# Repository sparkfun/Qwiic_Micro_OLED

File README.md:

SparkFun SparkFun Micro OLED Breakout (Qwiic)
========================================

[*SparkFun Micro OLED Breakout (Qwiic) (LCD-22495)*](https://www.sparkfun.com/products/22495)

The SparkFun Qwiic Micro OLED Breakout is a Qwiic-enabled version of our popular Micro OLED display! The small monochrome, blue-on-black OLED screen presents incredibly clear images for your viewing pleasure. 

Repository Contents
-------------------

* **/Hardware** - Eagle design files (.brd, .sch)
* **/Libraries** - Libraries for use with the SparkFun Micro OLED Breakout (Qwiic)
* **/Production** - Production panel files (.brd)
* **/Software** - Related software for the SparkFun Micro OLED Breakout (Qwiic).

Documentation
--------------
* **[Micro OLED Breakout Library](https://github.com/sparkfun/SparkFun_Micro_OLED_Arduino_Library)** - Latest Arduino library for the Micro OLED Breakout.
* **[Qwiic Micro OLED Breakout Library](https://github.com/sparkfun/SparkFun_Qwiic_OLED_Arduino_Library)** - Alternative Arduino library for the Qwiic Micro OLED Breakout. This library is higher performance and handles memory better than the Micro OLED Arduino Library. This library also works with 2x other Qwiic OLEDs!!!
* **[SparkFun Fritzing Part](https://github.com/sparkfun/Fritzing_Parts/blob/main/products/22495_sfe_qwiic_micro_oled_breakout_top_view.fzpz)** - V11, top view
* **[SparkFun Fritzing Part](https://github.com/sparkfun/Fritzing_Parts/blob/main/products/14532_sfe_Qwiic_OLED_Breakout.fzpz)** - V10, bottom view
* **[Hookup Guide](https://learn.sparkfun.com/tutorials/qwiic-micro-oled-hookup-guide)** - Basic hookup guide for the SparkFun Micro OLED Breakout (Qwiic).

Product Versions
----------------
* [LCD-22495](https://www.sparkfun.com/products/22495) - SparkFun Qwiic Micro OLED Breakout, v11
* [LCD-14532](https://www.sparkfun.com/products/14532) - SparkFun Qwiic Micro OLED Breakout, v10
* [SPX-14269 (RETIRED)](https://www.sparkfun.com/products/14269) - SparkX Qwiic Micro OLED Breakout

License Information
-------------------

This product is _**open source**_! 

Please review the LICENSE.md file for license information. 

If you have any questions or concerns on licensing, please contact techsupport@sparkfun.com.

Distributed as-is; no warranty is given.

- Your friends at SparkFun.

_<COLLABORATION CREDIT>_

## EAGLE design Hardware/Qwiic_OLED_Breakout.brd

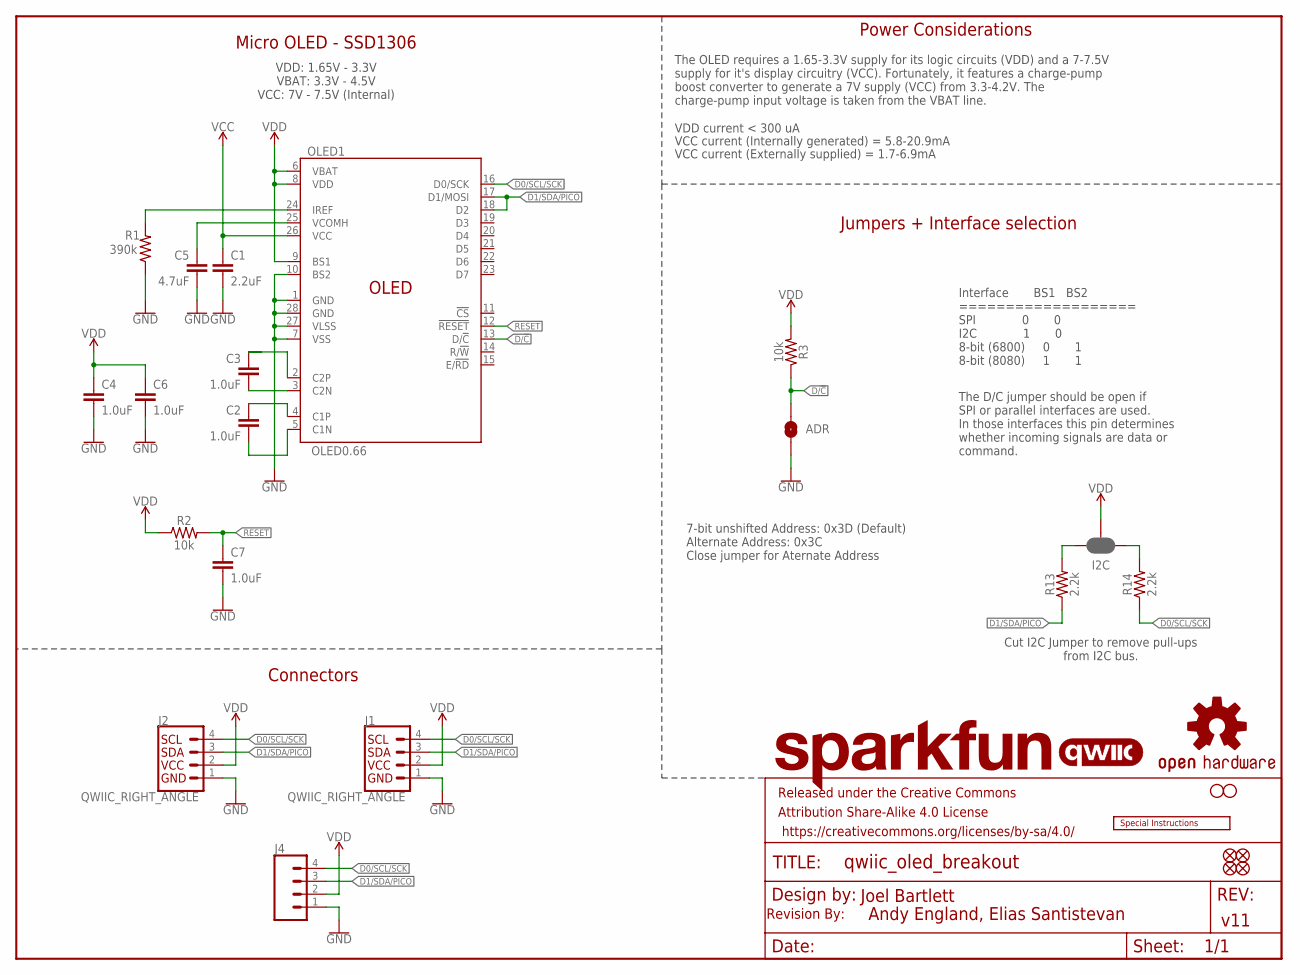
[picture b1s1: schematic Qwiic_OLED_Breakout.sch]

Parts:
ADR: JUMPER-SMT_2_NO_SILK; SMT-JUMPER_2_NO_SILK
C1: 2.2uF; 0805
C2, C3: 1.0uF; 0805
C4, C6, C7: 1.0uF; 0603
C5: 4.7uF; 1206
FID1, FID2, FID3, FID4: FIDUCIAL1X2; FIDUCIAL-1X2
FRAME1: FRAME-LETTER; CREATIVE_COMMONS
H1, H2: STAND-OFF
I2C: JUMPER-SMT_3_2-NC_PASTE_SILK; SMT-JUMPER_3_2-NC_PASTE_SILK
J1, J2: QWIIC_RIGHT_ANGLE; JST04_1MM_RA
J4: CONN_041X04_NO_SILK_NO_POP; 1X04_NO_SILK
LOGO2: SFE_LOGO_NAME.1_INCH; SFE_LOGO_NAME_.1
LOGO3: OSHW-LOGOS; OSHW-LOGO-S
LOGO5: QWIIC_LOGO_4MM; QWIIC_4MM
LOGO6: SPECIAL_INSTRUCTIONS-ORDERING; ORDERING_INSTRUCTIONS
OLED1: OLED0.66; OLED-0.66-64X48
R1: 390k; 0603
R2, R3: 10k; 0603
R13, R14: 2.2k; 0603

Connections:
C1P: C2.1, OLED1.4 (C1P)
C2N: C3.2, OLED1.3 (C2N)
D0/SCL/SCK: J1.4, J2.4, J4.4, OLED1.16 (D0/SCK), R14.1
D1/SDA/PICO: J1.3, J2.3, J4.3, OLED1.17 (D1/MOSI), OLED1.18 (D2), R13.1
D/!C!: ADR.2, OLED1.13 (D/!C!), R3.1
GND: ADR.1, C1.2, C4.2, C5.2, C6.2, C7.2, J1.1, J2.1, J4.1, OLED1.1 (GND), OLED1.7 (VSS), OLED1.10 (BS2), OLED1.27 (VLSS), OLED1.28 (GND), R1.1
IREF: OLED1.24 (IREF), R1.2
unnamed: C3.1, OLED1.2 (C2P)
unnamed: C2.2, OLED1.5 (C1N)
unnamed: I2C.3, R13.2
unnamed: I2C.1, R14.2
RESET: C7.1, OLED1.12 (!RESET!), R2.2
VCC: C1.1, OLED1.26 (VCC)
VCOMH: C5.1, OLED1.25 (VCOMH)
VDD: C4.1, C6.1, I2C.2, J1.2, J2.2, J4.2, OLED1.6 (VBAT), OLED1.8 (VDD), OLED1.9 (BS1), R2.1, R3.2

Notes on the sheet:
v11
VDD: 1.65V - 3.3V VBAT: 3.3V - 4.5V VCC: 7V - 7.5V (Internal)
VDD current < 300 uA
VCC current (Internally generated) = 5.8-20.9mA
VCC current (Externally supplied) = 1.7-6.9mA
Interface BS1 BS2 =================== SPI 0 0 I2C 1 0 8-bit (6800) 0 1 8-bit (8080) 1 1
Jumpers + Interface selection
7-bit unshifted Address: 0x3D (Default) Alternate Address: 0x3C Close jumper for Aternate Address
Power Considerations
The OLED requires a 1.65-3.3V supply for its logic circuits (VDD) and a 7-7.5V supply for it's display circuitry (VCC). Fortunately, it features a charge-pump boost converter to generate a 7V supply (VCC) from 3.3-4.2V. The charge-pump input voltage is taken from the VBAT line.
The D/C jumper should be open if SPI or parallel interfaces are used. In those interfaces this pin determines whether incoming signals are data or command.
Cut I2C Jumper to remove pull-ups from I2C bus.
Joel Bartlett
Andy England, Elias Santistevan
Connectors
Micro OLED - SSD1306
Revision By:

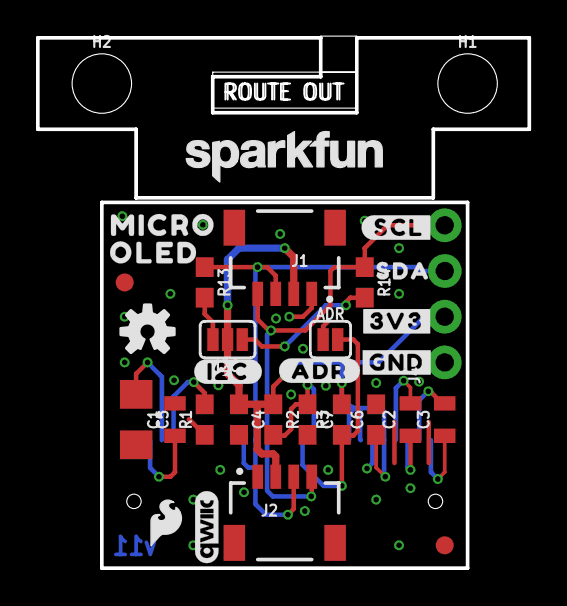
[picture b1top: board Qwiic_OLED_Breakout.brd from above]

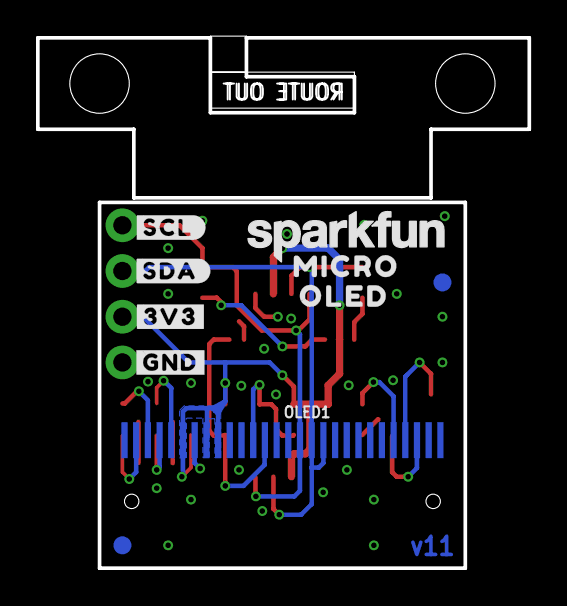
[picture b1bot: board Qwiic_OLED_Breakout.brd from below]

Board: 2 copper layers, 27.3 x 29.6 mm, 45 parts (10 on the bottom side), 15 nets.

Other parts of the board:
LOGO4: SFE_LOGO_NAME.1_INCH; SFE_LOGO_NAME_.1
U$1, U$13: MICRO593420
U$2, U$14: OLED593421
U$3: #ADR#5
U$4: #SCL#9
U$5, U$11: #3V3#1
U$6, U$12: #GND#0
U$7: SDA8
U$8: #I2C#1348
U$9: #SCL#8
U$10: #SDA#10
U$15: SFE_LOGO_FLAME_.1

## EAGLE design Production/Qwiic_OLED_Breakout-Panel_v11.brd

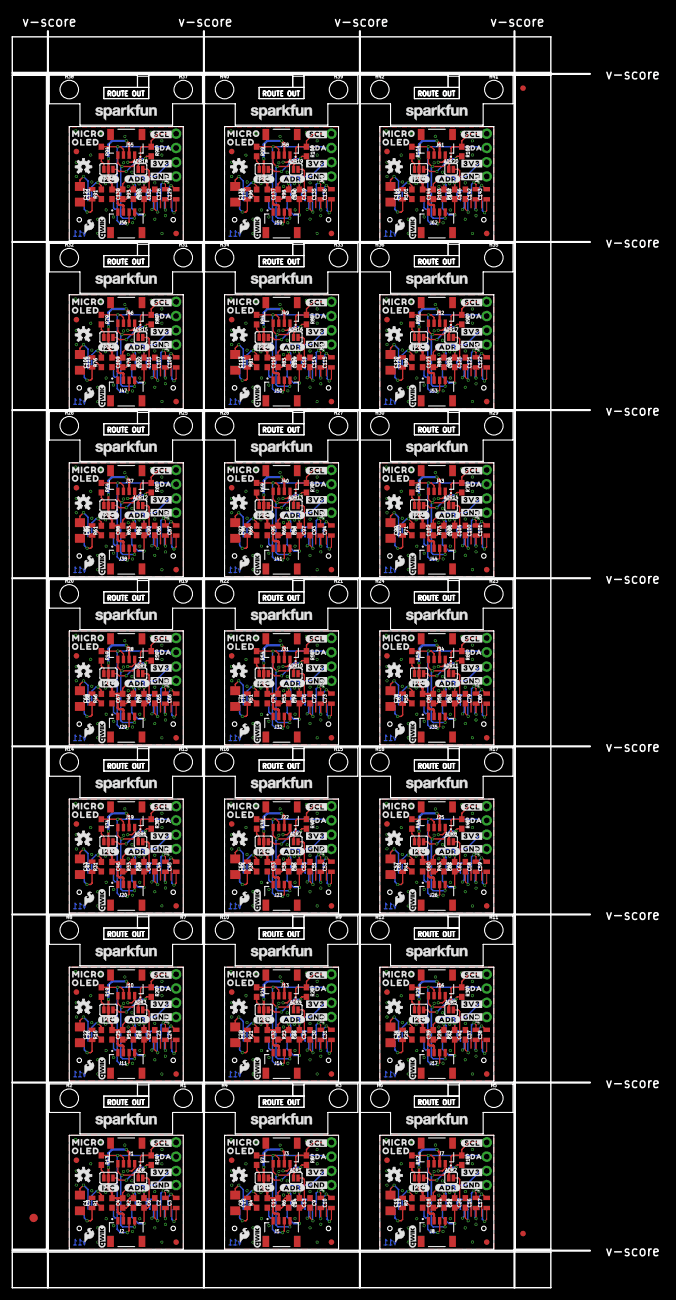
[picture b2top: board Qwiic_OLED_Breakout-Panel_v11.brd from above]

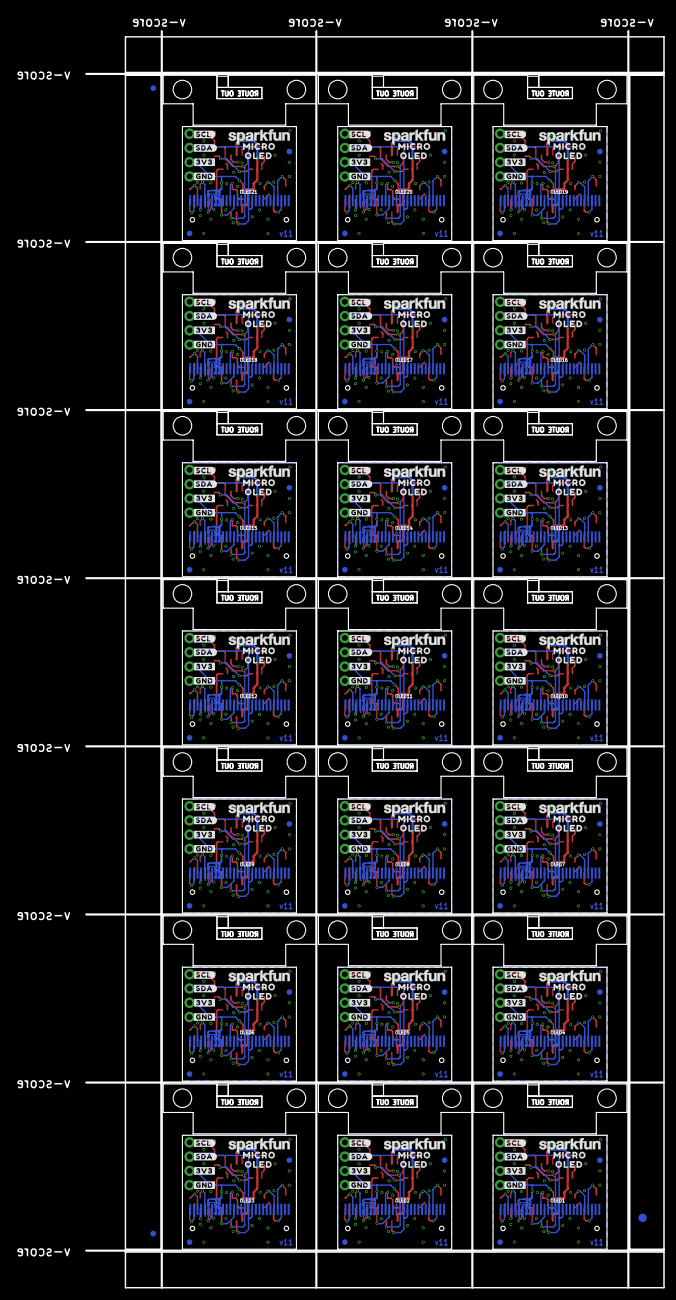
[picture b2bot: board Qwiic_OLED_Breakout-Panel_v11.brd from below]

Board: 2 copper layers, 103.0 x 224.0 mm, 909 parts (213 on the bottom side), 315 nets.

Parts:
ADR, ADR1, ADR2, ADR3, ADR4, ADR5, ADR6, ADR7, ADR8, ADR9, ADR10, ADR11, ADR12, ADR13, ADR14, ADR15, ADR16, ADR17, ADR18, ADR19, ADR20: JUMPER-SMT_2_NO_SILK; SMT-JUMPER_2_NO_SILK
C1, C8, C15, C22, C29, C36, C43, C50, C57, C64, C71, C78, C85, C92, C99, C106, C113, C120, C127, C134, C141: 2.2uF; 0805
C2, C3, C9, C10, C16, C17, C23, C24, C30, C31, C37, C38, C44, C45, C51, C52, C58, C59, C65, C66, C72, C73, C79, C80, C86, C87, C93, C94, C100, C101, C107, C108, C114, C115, C121, C122, C128, C129, C135, C136, C142, C143: 1.0uF; 0805
C4, C6, C7, C11, C13, C14, C18, C20, C21, C25, C27, C28, C32, C34, C35, C39, C41, C42, C46, C48, C49, C53, C55, C56, C60, C62, C63, C67, C69, C70, C74, C76, C77, C81, C83, C84, C88, C90, C91, C95, C97, C98, C102, C104, C105, C109, C111, C112, C116, C118, C119, C123, C125, C126, C130, C132, C133, C137, C139, C140, C144, C146, C147: 1.0uF; 0603
C5, C12, C19, C26, C33, C40, C47, C54, C61, C68, C75, C82, C89, C96, C103, C110, C117, C124, C131, C138, C145: 4.7uF; 1206
E$1, E$2, E$3, E$4: FIDUCIAL-1X2
E$5, E$6: FIDUCIAL-1.5X3
FID1, FID2, FID3, FID4, FID5, FID6, FID7, FID8, FID9, FID10, FID11, FID12, FID13, FID14, FID15, FID16, FID17, FID18, FID19, FID20, FID21, FID22, FID23, FID24, FID25, FID26, FID27, FID28, FID29, FID30, FID31, FID32, FID33, FID34, FID35, FID36, FID37, FID38, FID39, FID40, FID41, FID42, FID43, FID44, FID45, FID46, FID47, FID48, FID49, FID50, FID51, FID52, FID53, FID54, FID55, FID56, FID57, FID58, FID59, FID60, FID61, FID62, FID63, FID64, FID65, FID66, FID67, FID68, FID69, FID70, FID71, FID72, FID73, FID74, FID75, FID76, FID77, FID78, FID79, FID80, FID81, FID82, FID83, FID84: FIDUCIAL1X2; FIDUCIAL-1X2
H1, H2, H3, H4, H5, H6, H7, H8, H9, H10, H11, H12, H13, H14, H15, H16, H17, H18, H19, H20, H21, H22, H23, H24, H25, H26, H27, H28, H29, H30, H31, H32, H33, H34, H35, H36, H37, H38, H39, H40, H41, H42: STAND-OFF
I2C, I2C1, I2C2, I2C3, I2C4, I2C5, I2C6, I2C7, I2C8, I2C9, I2C10, I2C11, I2C12, I2C13, I2C14, I2C15, I2C16, I2C17, I2C18, I2C19, I2C20: JUMPER-SMT_3_2-NC_PASTE_SILK; SMT-JUMPER_3_2-NC_PASTE_SILK
J1, J2, J3, J5, J7, J8, J10, J11, J13, J14, J16, J17, J19, J20, J22, J23, J25, J26, J28, J29, J31, J32, J34, J35, J37, J38, J40, J41, J43, J44, J46, J47, J49, J50, J52, J53, J55, J56, J58, J59, J61, J62: QWIIC_RIGHT_ANGLE; JST04_1MM_RA
J4, J6, J9, J12, J15, J18, J21, J24, J27, J30, J33, J36, J39, J42, J45, J48, J51, J54, J57, J60, J63: 1X04_NO_SILK
LOGO1, LOGO3, LOGO9, LOGO13, LOGO17, LOGO21, LOGO25, LOGO29, LOGO33, LOGO37, LOGO41, LOGO45, LOGO49, LOGO53, LOGO57, LOGO61, LOGO65, LOGO69, LOGO73, LOGO77, LOGO81: OSHW-LOGOS; OSHW-LOGO-S
LOGO2, LOGO4, LOGO7, LOGO8, LOGO11, LOGO12, LOGO15, LOGO16, LOGO19, LOGO20, LOGO23, LOGO24, LOGO27, LOGO28, LOGO31, LOGO32, LOGO35, LOGO36, LOGO39, LOGO40, LOGO43, LOGO44, LOGO47, LOGO48, LOGO51, LOGO52, LOGO55, LOGO56, LOGO59, LOGO60, LOGO63, LOGO64, LOGO67, LOGO68, LOGO71, LOGO72, LOGO75, LOGO76, LOGO79, LOGO80, LOGO83, LOGO84: SFE_LOGO_NAME.1_INCH; SFE_LOGO_NAME_.1
LOGO5, LOGO6, LOGO10, LOGO14, LOGO18, LOGO22, LOGO26, LOGO30, LOGO34, LOGO38, LOGO42, LOGO46, LOGO50, LOGO54, LOGO58, LOGO62, LOGO66, LOGO70, LOGO74, LOGO78, LOGO82: QWIIC_LOGO_4MM; QWIIC_4MM
OLED1, OLED2, OLED3, OLED4, OLED5, OLED6, OLED7, OLED8, OLED9, OLED10, OLED11, OLED12, OLED13, OLED14, OLED15, OLED16, OLED17, OLED18, OLED19, OLED20, OLED21: OLED0.66; OLED-0.66-64X48
R1, R4, R9, R16, R21, R26, R31, R36, R41, R46, R51, R56, R61, R66, R71, R76, R81, R86, R91, R96, R101: 390k; 0603
R2, R3, R5, R6, R10, R11, R17, R18, R22, R23, R27, R28, R32, R33, R37, R38, R42, R43, R47, R48, R52, R53, R57, R58, R62, R63, R67, R68, R72, R73, R77, R78, R82, R83, R87, R88, R92, R93, R97, R98, R102, R103: 10k; 0603
R7, R8, R12, R13, R14, R15, R19, R20, R24, R25, R29, R30, R34, R35, R39, R40, R44, R45, R49, R50, R54, R55, R59, R60, R64, R65, R69, R70, R74, R75, R79, R80, R84, R85, R89, R90, R94, R95, R99, R100, R104, R105: 2.2k; 0603
U$1, U$13, U$16, U$28, U$31, U$43, U$46, U$58, U$61, U$73, U$76, U$88, U$91, U$103, U$106, U$118, U$121, U$133, U$136, U$148, U$151, U$163, U$166, U$178, U$181, U$193, U$196, U$208, U$211, U$223, U$226, U$238, U$241, U$253, U$256, U$268, U$271, U$283, U$286, U$298, U$301, U$313: MICRO593420
U$2, U$14, U$17, U$29, U$32, U$44, U$47, U$59, U$62, U$74, U$77, U$89, U$92, U$104, U$107, U$119, U$122, U$134, U$137, U$149, U$152, U$164, U$167, U$179, U$182, U$194, U$197, U$209, U$212, U$224, U$227, U$239, U$242, U$254, U$257, U$269, U$272, U$284, U$287, U$299, U$302, U$314: OLED593421
U$3, U$18, U$33, U$48, U$63, U$78, U$93, U$108, U$123, U$138, U$153, U$168, U$183, U$198, U$213, U$228, U$243, U$258, U$273, U$288, U$303: #ADR#5
U$4, U$19, U$34, U$49, U$64, U$79, U$94, U$109, U$124, U$139, U$154, U$169, U$184, U$199, U$214, U$229, U$244, U$259, U$274, U$289, U$304: #SCL#9
U$5, U$11, U$20, U$26, U$35, U$41, U$50, U$56, U$65, U$71, U$80, U$86, U$95, U$101, U$110, U$116, U$125, U$131, U$140, U$146, U$155, U$161, U$170, U$176, U$185, U$191, U$200, U$206, U$215, U$221, U$230, U$236, U$245, U$251, U$260, U$266, U$275, U$281, U$290, U$296, U$305, U$311: #3V3#1
U$6, U$12, U$21, U$27, U$36, U$42, U$51, U$57, U$66, U$72, U$81, U$87, U$96, U$102, U$111, U$117, U$126, U$132, U$141, U$147, U$156, U$162, U$171, U$177, U$186, U$192, U$201, U$207, U$216, U$222, U$231, U$237, U$246, U$252, U$261, U$267, U$276, U$282, U$291, U$297, U$306, U$312: #GND#0
U$7, U$22, U$37, U$52, U$67, U$82, U$97, U$112, U$127, U$142, U$157, U$172, U$187, U$202, U$217, U$232, U$247, U$262, U$277, U$292, U$307: SDA8
U$8, U$23, U$38, U$53, U$68, U$83, U$98, U$113, U$128, U$143, U$158, U$173, U$188, U$203, U$218, U$233, U$248, U$263, U$278, U$293, U$308: #I2C#1348
U$9, U$24, U$39, U$54, U$69, U$84, U$99, U$114, U$129, U$144, U$159, U$174, U$189, U$204, U$219, U$234, U$249, U$264, U$279, U$294, U$309: #SCL#8
U$10, U$25, U$40, U$55, U$70, U$85, U$100, U$115, U$130, U$145, U$160, U$175, U$190, U$205, U$220, U$235, U$250, U$265, U$280, U$295, U$310: #SDA#10
U$15, U$30, U$45, U$60, U$75, U$90, U$105, U$120, U$135, U$150, U$165, U$180, U$195, U$210, U$225, U$240, U$255, U$270, U$285, U$300, U$315: SFE_LOGO_FLAME_.1

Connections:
C1P: C2.1, OLED1.4
C1P1: C9.1, OLED2.4
C1P2: C16.1, OLED3.4
C1P3: C23.1, OLED4.4
C1P4: C30.1, OLED5.4
C1P5: C37.1, OLED6.4
C1P6: C44.1, OLED7.4
C1P7: C51.1, OLED8.4
C1P8: C58.1, OLED9.4
C1P9: C65.1, OLED10.4
C1P10: C72.1, OLED11.4
C1P11: C79.1, OLED12.4
C1P12: C86.1, OLED13.4
C1P13: C93.1, OLED14.4
C1P14: C100.1, OLED15.4
C1P15: C107.1, OLED16.4
C1P16: C114.1, OLED17.4
C1P17: C121.1, OLED18.4
C1P18: C128.1, OLED19.4
C1P19: C135.1, OLED20.4
C1P20: C142.1, OLED21.4
C2N: C3.2, OLED1.3
C2N1: C10.2, OLED2.3
C2N2: C17.2, OLED3.3
C2N3: C24.2, OLED4.3
C2N4: C31.2, OLED5.3
C2N5: C38.2, OLED6.3
C2N6: C45.2, OLED7.3
C2N7: C52.2, OLED8.3
C2N8: C59.2, OLED9.3
C2N9: C66.2, OLED10.3
C2N10: C73.2, OLED11.3
C2N11: C80.2, OLED12.3
C2N12: C87.2, OLED13.3
C2N13: C94.2, OLED14.3
C2N14: C101.2, OLED15.3
C2N15: C108.2, OLED16.3
C2N16: C115.2, OLED17.3
C2N17: C122.2, OLED18.3
C2N18: C129.2, OLED19.3
C2N19: C136.2, OLED20.3
C2N20: C143.2, OLED21.3
D0/SCL/SCK: J1.4, J2.4, J4.4, OLED1.16, R14.1
D0/SCL/SCK1: J3.4, J5.4, J6.4, OLED2.16, R8.1
D0/SCL/SCK2: J7.4, J8.4, J9.4, OLED3.16, R15.1
D0/SCL/SCK3: J10.4, J11.4, J12.4, OLED4.16, R20.1
D0/SCL/SCK4: J13.4, J14.4, J15.4, OLED5.16, R25.1
D0/SCL/SCK5: J16.4, J17.4, J18.4, OLED6.16, R30.1
D0/SCL/SCK6: J19.4, J20.4, J21.4, OLED7.16, R35.1
D0/SCL/SCK7: J22.4, J23.4, J24.4, OLED8.16, R40.1
D0/SCL/SCK8: J25.4, J26.4, J27.4, OLED9.16, R45.1
D0/SCL/SCK9: J28.4, J29.4, J30.4, OLED10.16, R50.1
D0/SCL/SCK10: J31.4, J32.4, J33.4, OLED11.16, R55.1
D0/SCL/SCK11: J34.4, J35.4, J36.4, OLED12.16, R60.1
D0/SCL/SCK12: J37.4, J38.4, J39.4, OLED13.16, R65.1
D0/SCL/SCK13: J40.4, J41.4, J42.4, OLED14.16, R70.1
D0/SCL/SCK14: J43.4, J44.4, J45.4, OLED15.16, R75.1
D0/SCL/SCK15: J46.4, J47.4, J48.4, OLED16.16, R80.1
D0/SCL/SCK16: J49.4, J50.4, J51.4, OLED17.16, R85.1
D0/SCL/SCK17: J52.4, J53.4, J54.4, OLED18.16, R90.1
D0/SCL/SCK18: J55.4, J56.4, J57.4, OLED19.16, R95.1
D0/SCL/SCK19: J58.4, J59.4, J60.4, OLED20.16, R100.1
D0/SCL/SCK20: J61.4, J62.4, J63.4, OLED21.16, R105.1
D1/SDA/PICO: J1.3, J2.3, J4.3, OLED1.17, OLED1.18, R13.1
D1/SDA/PICO1: J3.3, J5.3, J6.3, OLED2.17, OLED2.18, R7.1
D1/SDA/PICO2: J7.3, J8.3, J9.3, OLED3.17, OLED3.18, R12.1
D1/SDA/PICO3: J10.3, J11.3, J12.3, OLED4.17, OLED4.18, R19.1
D1/SDA/PICO4: J13.3, J14.3, J15.3, OLED5.17, OLED5.18, R24.1
D1/SDA/PICO5: J16.3, J17.3, J18.3, OLED6.17, OLED6.18, R29.1
D1/SDA/PICO6: J19.3, J20.3, J21.3, OLED7.17, OLED7.18, R34.1
D1/SDA/PICO7: J22.3, J23.3, J24.3, OLED8.17, OLED8.18, R39.1
D1/SDA/PICO8: J25.3, J26.3, J27.3, OLED9.17, OLED9.18, R44.1
D1/SDA/PICO9: J28.3, J29.3, J30.3, OLED10.17, OLED10.18, R49.1
D1/SDA/PICO10: J31.3, J32.3, J33.3, OLED11.17, OLED11.18, R54.1
D1/SDA/PICO11: J34.3, J35.3, J36.3, OLED12.17, OLED12.18, R59.1
D1/SDA/PICO12: J37.3, J38.3, J39.3, OLED13.17, OLED13.18, R64.1
D1/SDA/PICO13: J40.3, J41.3, J42.3, OLED14.17, OLED14.18, R69.1
D1/SDA/PICO14: J43.3, J44.3, J45.3, OLED15.17, OLED15.18, R74.1
D1/SDA/PICO15: J46.3, J47.3, J48.3, OLED16.17, OLED16.18, R79.1
D1/SDA/PICO16: J49.3, J50.3, J51.3, OLED17.17, OLED17.18, R84.1
D1/SDA/PICO17: J52.3, J53.3, J54.3, OLED18.17, OLED18.18, R89.1
D1/SDA/PICO18: J55.3, J56.3, J57.3, OLED19.17, OLED19.18, R94.1
D1/SDA/PICO19: J58.3, J59.3, J60.3, OLED20.17, OLED20.18, R99.1
D1/SDA/PICO20: J61.3, J62.3, J63.3, OLED21.17, OLED21.18, R104.1
D/!C!: ADR.2, OLED1.13, R3.1
D/!C!1: ADR1.2, OLED2.13, R5.1
D/!C!2: ADR2.2, OLED3.13, R10.1
D/!C!3: ADR3.2, OLED4.13, R17.1
D/!C!4: ADR4.2, OLED5.13, R22.1
D/!C!5: ADR5.2, OLED6.13, R27.1
D/!C!6: ADR6.2, OLED7.13, R32.1
D/!C!7: ADR7.2, OLED8.13, R37.1
D/!C!8: ADR8.2, OLED9.13, R42.1
D/!C!9: ADR9.2, OLED10.13, R47.1
D/!C!10: ADR10.2, OLED11.13, R52.1
D/!C!11: ADR11.2, OLED12.13, R57.1
D/!C!12: ADR12.2, OLED13.13, R62.1
D/!C!13: ADR13.2, OLED14.13, R67.1
D/!C!14: ADR14.2, OLED15.13, R72.1
D/!C!15: ADR15.2, OLED16.13, R77.1
D/!C!16: ADR16.2, OLED17.13, R82.1
D/!C!17: ADR17.2, OLED18.13, R87.1
D/!C!18: ADR18.2, OLED19.13, R92.1
D/!C!19: ADR19.2, OLED20.13, R97.1
D/!C!20: ADR20.2, OLED21.13, R102.1
GND: ADR.1, C1.2, C4.2, C5.2, C6.2, C7.2, J1.1, J2.1, J4.1, OLED1.1, OLED1.7, OLED1.10, OLED1.27, OLED1.28, R1.1
GND1: ADR1.1, C8.2, C11.2, C12.2, C13.2, C14.2, J3.1, J5.1, J6.1, OLED2.1, OLED2.7, OLED2.10, OLED2.27, OLED2.28, R4.1
GND2: ADR2.1, C15.2, C18.2, C19.2, C20.2, C21.2, J7.1, J8.1, J9.1, OLED3.1, OLED3.7, OLED3.10, OLED3.27, OLED3.28, R9.1
GND3: ADR3.1, C22.2, C25.2, C26.2, C27.2, C28.2, J10.1, J11.1, J12.1, OLED4.1, OLED4.7, OLED4.10, OLED4.27, OLED4.28, R16.1
GND4: ADR4.1, C29.2, C32.2, C33.2, C34.2, C35.2, J13.1, J14.1, J15.1, OLED5.1, OLED5.7, OLED5.10, OLED5.27, OLED5.28, R21.1
GND5: ADR5.1, C36.2, C39.2, C40.2, C41.2, C42.2, J16.1, J17.1, J18.1, OLED6.1, OLED6.7, OLED6.10, OLED6.27, OLED6.28, R26.1
GND6: ADR6.1, C43.2, C46.2, C47.2, C48.2, C49.2, J19.1, J20.1, J21.1, OLED7.1, OLED7.7, OLED7.10, OLED7.27, OLED7.28, R31.1
GND7: ADR7.1, C50.2, C53.2, C54.2, C55.2, C56.2, J22.1, J23.1, J24.1, OLED8.1, OLED8.7, OLED8.10, OLED8.27, OLED8.28, R36.1
GND8: ADR8.1, C57.2, C60.2, C61.2, C62.2, C63.2, J25.1, J26.1, J27.1, OLED9.1, OLED9.7, OLED9.10, OLED9.27, OLED9.28, R41.1
GND9: ADR9.1, C64.2, C67.2, C68.2, C69.2, C70.2, J28.1, J29.1, J30.1, OLED10.1, OLED10.7, OLED10.10, OLED10.27, OLED10.28, R46.1
GND10: ADR10.1, C71.2, C74.2, C75.2, C76.2, C77.2, J31.1, J32.1, J33.1, OLED11.1, OLED11.7, OLED11.10, OLED11.27, OLED11.28, R51.1
GND11: ADR11.1, C78.2, C81.2, C82.2, C83.2, C84.2, J34.1, J35.1, J36.1, OLED12.1, OLED12.7, OLED12.10, OLED12.27, OLED12.28, R56.1
GND12: ADR12.1, C85.2, C88.2, C89.2, C90.2, C91.2, J37.1, J38.1, J39.1, OLED13.1, OLED13.7, OLED13.10, OLED13.27, OLED13.28, R61.1
GND13: ADR13.1, C92.2, C95.2, C96.2, C97.2, C98.2, J40.1, J41.1, J42.1, OLED14.1, OLED14.7, OLED14.10, OLED14.27, OLED14.28, R66.1
GND14: ADR14.1, C99.2, C102.2, C103.2, C104.2, C105.2, J43.1, J44.1, J45.1, OLED15.1, OLED15.7, OLED15.10, OLED15.27, OLED15.28, R71.1
GND15: ADR15.1, C106.2, C109.2, C110.2, C111.2, C112.2, J46.1, J47.1, J48.1, OLED16.1, OLED16.7, OLED16.10, OLED16.27, OLED16.28, R76.1
GND16: ADR16.1, C113.2, C116.2, C117.2, C118.2, C119.2, J49.1, J50.1, J51.1, OLED17.1, OLED17.7, OLED17.10, OLED17.27, OLED17.28, R81.1
GND17: ADR17.1, C120.2, C123.2, C124.2, C125.2, C126.2, J52.1, J53.1, J54.1, OLED18.1, OLED18.7, OLED18.10, OLED18.27, OLED18.28, R86.1
GND18: ADR18.1, C127.2, C130.2, C131.2, C132.2, C133.2, J55.1, J56.1, J57.1, OLED19.1, OLED19.7, OLED19.10, OLED19.27, OLED19.28, R91.1
GND19: ADR19.1, C134.2, C137.2, C138.2, C139.2, C140.2, J58.1, J59.1, J60.1, OLED20.1, OLED20.7, OLED20.10, OLED20.27, OLED20.28, R96.1
GND20: ADR20.1, C141.2, C144.2, C145.2, C146.2, C147.2, J61.1, J62.1, J63.1, OLED21.1, OLED21.7, OLED21.10, OLED21.27, OLED21.28, R101.1
IREF: OLED1.24, R1.2
IREF1: OLED2.24, R4.2
IREF2: OLED3.24, R9.2
IREF3: OLED4.24, R16.2
IREF4: OLED5.24, R21.2
IREF5: OLED6.24, R26.2
IREF6: OLED7.24, R31.2
IREF7: OLED8.24, R36.2
IREF8: OLED9.24, R41.2
IREF9: OLED10.24, R46.2
IREF10: OLED11.24, R51.2
IREF11: OLED12.24, R56.2
IREF12: OLED13.24, R61.2
IREF13: OLED14.24, R66.2
IREF14: OLED15.24, R71.2
IREF15: OLED16.24, R76.2
IREF16: OLED17.24, R81.2
IREF17: OLED18.24, R86.2
IREF18: OLED19.24, R91.2
IREF19: OLED20.24, R96.2
IREF20: OLED21.24, R101.2
unnamed: C3.1, OLED1.2
unnamed: C2.2, OLED1.5
unnamed: I2C1.3, R7.2
unnamed: I2C.3, R13.2
unnamed: I2C.1, R14.2
unnamed: I2C1.1, R8.2
unnamed: C10.1, OLED2.2
unnamed: C9.2, OLED2.5
unnamed: I2C2.3, R12.2
unnamed: I2C2.1, R15.2
unnamed: C17.1, OLED3.2
unnamed: C16.2, OLED3.5
unnamed: I2C3.3, R19.2
unnamed: I2C3.1, R20.2
unnamed: C24.1, OLED4.2
unnamed: C23.2, OLED4.5
unnamed: I2C4.3, R24.2
unnamed: I2C4.1, R25.2
unnamed: C31.1, OLED5.2
unnamed: C30.2, OLED5.5
unnamed: I2C5.3, R29.2
unnamed: I2C5.1, R30.2
unnamed: C38.1, OLED6.2
unnamed: C37.2, OLED6.5
unnamed: I2C6.3, R34.2
unnamed: I2C6.1, R35.2
unnamed: C45.1, OLED7.2
unnamed: C44.2, OLED7.5
unnamed: I2C7.3, R39.2
unnamed: I2C7.1, R40.2
unnamed: C52.1, OLED8.2
unnamed: C51.2, OLED8.5
unnamed: I2C8.3, R44.2
unnamed: I2C8.1, R45.2
unnamed: C59.1, OLED9.2
unnamed: C58.2, OLED9.5
unnamed: I2C9.3, R49.2
unnamed: I2C9.1, R50.2
unnamed: C66.1, OLED10.2
unnamed: C65.2, OLED10.5
unnamed: I2C10.3, R54.2
unnamed: I2C10.1, R55.2
unnamed: C73.1, OLED11.2
unnamed: C72.2, OLED11.5
unnamed: I2C11.3, R59.2
unnamed: I2C11.1, R60.2
unnamed: C80.1, OLED12.2
unnamed: C79.2, OLED12.5
unnamed: I2C12.3, R64.2
unnamed: I2C12.1, R65.2
unnamed: C87.1, OLED13.2
unnamed: C86.2, OLED13.5
unnamed: I2C13.3, R69.2
unnamed: I2C13.1, R70.2
unnamed: C94.1, OLED14.2
unnamed: C93.2, OLED14.5
unnamed: I2C14.3, R74.2
unnamed: I2C14.1, R75.2
unnamed: C101.1, OLED15.2
unnamed: C100.2, OLED15.5
unnamed: I2C15.3, R79.2
unnamed: I2C15.1, R80.2
unnamed: C108.1, OLED16.2
unnamed: C107.2, OLED16.5
unnamed: I2C16.3, R84.2
unnamed: I2C16.1, R85.2
unnamed: C115.1, OLED17.2
unnamed: C114.2, OLED17.5
unnamed: I2C17.3, R89.2
unnamed: I2C17.1, R90.2
unnamed: C122.1, OLED18.2
unnamed: C121.2, OLED18.5
unnamed: I2C18.3, R94.2
unnamed: I2C18.1, R95.2
unnamed: C129.1, OLED19.2
unnamed: C128.2, OLED19.5
unnamed: I2C19.3, R99.2
unnamed: I2C19.1, R100.2
unnamed: C136.1, OLED20.2
unnamed: C135.2, OLED20.5
unnamed: I2C20.3, R104.2
unnamed: I2C20.1, R105.2
unnamed: C143.1, OLED21.2
unnamed: C142.2, OLED21.5
RESET: C7.1, OLED1.12, R2.2
RESET1: C14.1, OLED2.12, R6.2
RESET2: C21.1, OLED3.12, R11.2
RESET3: C28.1, OLED4.12, R18.2
RESET4: C35.1, OLED5.12, R23.2
RESET5: C42.1, OLED6.12, R28.2
RESET6: C49.1, OLED7.12, R33.2
RESET7: C56.1, OLED8.12, R38.2
RESET8: C63.1, OLED9.12, R43.2
RESET9: C70.1, OLED10.12, R48.2
RESET10: C77.1, OLED11.12, R53.2
RESET11: C84.1, OLED12.12, R58.2
RESET12: C91.1, OLED13.12, R63.2
RESET13: C98.1, OLED14.12, R68.2
RESET14: C105.1, OLED15.12, R73.2
RESET15: C112.1, OLED16.12, R78.2
RESET16: C119.1, OLED17.12, R83.2
RESET17: C126.1, OLED18.12, R88.2
RESET18: C133.1, OLED19.12, R93.2
RESET19: C140.1, OLED20.12, R98.2
RESET20: C147.1, OLED21.12, R103.2
VCC: C1.1, OLED1.26
VCC1: C8.1, OLED2.26
VCC2: C15.1, OLED3.26
VCC3: C22.1, OLED4.26
VCC4: C29.1, OLED5.26
VCC5: C36.1, OLED6.26
VCC6: C43.1, OLED7.26
VCC7: C50.1, OLED8.26
VCC8: C57.1, OLED9.26
VCC9: C64.1, OLED10.26
VCC10: C71.1, OLED11.26
VCC11: C78.1, OLED12.26
VCC12: C85.1, OLED13.26
VCC13: C92.1, OLED14.26
VCC14: C99.1, OLED15.26
VCC15: C106.1, OLED16.26
VCC16: C113.1, OLED17.26
VCC17: C120.1, OLED18.26
VCC18: C127.1, OLED19.26
VCC19: C134.1, OLED20.26
VCC20: C141.1, OLED21.26
VCOMH: C5.1, OLED1.25
VCOMH1: C12.1, OLED2.25
VCOMH2: C19.1, OLED3.25
VCOMH3: C26.1, OLED4.25
VCOMH4: C33.1, OLED5.25
VCOMH5: C40.1, OLED6.25
VCOMH6: C47.1, OLED7.25
VCOMH7: C54.1, OLED8.25
VCOMH8: C61.1, OLED9.25
VCOMH9: C68.1, OLED10.25
VCOMH10: C75.1, OLED11.25
VCOMH11: C82.1, OLED12.25
VCOMH12: C89.1, OLED13.25
VCOMH13: C96.1, OLED14.25
VCOMH14: C103.1, OLED15.25
VCOMH15: C110.1, OLED16.25
VCOMH16: C117.1, OLED17.25
VCOMH17: C124.1, OLED18.25
VCOMH18: C131.1, OLED19.25
VCOMH19: C138.1, OLED20.25
VCOMH20: C145.1, OLED21.25
VDD: C4.1, C6.1, I2C.2, J1.2, J2.2, J4.2, OLED1.6, OLED1.8, OLED1.9, R2.1, R3.2
VDD1: C11.1, C13.1, I2C1.2, J3.2, J5.2, J6.2, OLED2.6, OLED2.8, OLED2.9, R5.2, R6.1
VDD2: C18.1, C20.1, I2C2.2, J7.2, J8.2, J9.2, OLED3.6, OLED3.8, OLED3.9, R10.2, R11.1
VDD3: C25.1, C27.1, I2C3.2, J10.2, J11.2, J12.2, OLED4.6, OLED4.8, OLED4.9, R17.2, R18.1
VDD4: C32.1, C34.1, I2C4.2, J13.2, J14.2, J15.2, OLED5.6, OLED5.8, OLED5.9, R22.2, R23.1
VDD5: C39.1, C41.1, I2C5.2, J16.2, J17.2, J18.2, OLED6.6, OLED6.8, OLED6.9, R27.2, R28.1
VDD6: C46.1, C48.1, I2C6.2, J19.2, J20.2, J21.2, OLED7.6, OLED7.8, OLED7.9, R32.2, R33.1
VDD7: C53.1, C55.1, I2C7.2, J22.2, J23.2, J24.2, OLED8.6, OLED8.8, OLED8.9, R37.2, R38.1
VDD8: C60.1, C62.1, I2C8.2, J25.2, J26.2, J27.2, OLED9.6, OLED9.8, OLED9.9, R42.2, R43.1
VDD9: C67.1, C69.1, I2C9.2, J28.2, J29.2, J30.2, OLED10.6, OLED10.8, OLED10.9, R47.2, R48.1
VDD10: C74.1, C76.1, I2C10.2, J31.2, J32.2, J33.2, OLED11.6, OLED11.8, OLED11.9, R52.2, R53.1
VDD11: C81.1, C83.1, I2C11.2, J34.2, J35.2, J36.2, OLED12.6, OLED12.8, OLED12.9, R57.2, R58.1
VDD12: C88.1, C90.1, I2C12.2, J37.2, J38.2, J39.2, OLED13.6, OLED13.8, OLED13.9, R62.2, R63.1
VDD13: C95.1, C97.1, I2C13.2, J40.2, J41.2, J42.2, OLED14.6, OLED14.8, OLED14.9, R67.2, R68.1
VDD14: C102.1, C104.1, I2C14.2, J43.2, J44.2, J45.2, OLED15.6, OLED15.8, OLED15.9, R72.2, R73.1
VDD15: C109.1, C111.1, I2C15.2, J46.2, J47.2, J48.2, OLED16.6, OLED16.8, OLED16.9, R77.2, R78.1
VDD16: C116.1, C118.1, I2C16.2, J49.2, J50.2, J51.2, OLED17.6, OLED17.8, OLED17.9, R82.2, R83.1
VDD17: C123.1, C125.1, I2C17.2, J52.2, J53.2, J54.2, OLED18.6, OLED18.8, OLED18.9, R87.2, R88.1
VDD18: C130.1, C132.1, I2C18.2, J55.2, J56.2, J57.2, OLED19.6, OLED19.8, OLED19.9, R92.2, R93.1
VDD19: C137.1, C139.1, I2C19.2, J58.2, J59.2, J60.2, OLED20.6, OLED20.8, OLED20.9, R97.2, R98.1
VDD20: C144.1, C146.1, I2C20.2, J61.2, J62.2, J63.2, OLED21.6, OLED21.8, OLED21.9, R102.2, R103.1

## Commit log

2017-11-02 getting rid of unnecessary files
2017-11-03 Pre-design Review
2017-11-07 Post Checklist Changes
2017-11-30 Checklist
2017-12-04 Checklist issues fixed
2017-12-04 fixed vscore
2017-12-04 Panel
2018-01-17 Squashed 'Libraries/Arduino/' content from commit 6ccbba3
    git-subtree-dir: Libraries/Arduino
    git-subtree-split: 6ccbba3deb1936ea34ce9319320bb4e321c3da03
2018-01-19 Update README.md
    update images and links.
2018-01-19 Delete README.md
    Removing since there is no Enclosure for the Qwiic Micro OLED
2018-01-19 cleaned repo
2018-01-19 Update README.md
    link SparkX Qwiic Micro OLED Breakout board in the product versions.
2019-04-24 Remove old library files. Add link to current lib in readme.
2019-04-24 Fix link to library in readme
2023-05-05 Expands the distance between the standoff 0.5" to adhere to our Qwiic standard
    * Updates silk
    * Organizes schematic
    * Adds ordering instructions
    * Adds additional measures and units for the measures
2023-05-05 Updates jumper library
2023-05-05 Updates D/C net
2023-05-05 Fixes mounting hole spacing (derp)
    * Adds more measures
    * Changes pull up resistor values
    * Fixes some notes on ordering instructions
    * Adds more notes and silk
    * Connects some GND pour
2023-05-08 Fixes some proportional text, cleans up some nets
2023-05-08 Updates the isolate, replaces the main OLED part, adds some polygons
2023-05-09 Moves Ordering Instructions
    * Updates notes in schematics
2023-05-09 Adds a single via
    * Gets judicious with the text in the schematic
2023-05-09 Approves DRC errors
2023-05-09 Adds "Revised By: " to the Board file
2023-05-09 Adds temporary production panel
2023-05-10 Adds new panel after bringing the tabbed part to match the panel
2023-05-10 Revised v11 panel to match v10 panel
    - Adjusted rail widths, board spacing, and fiducial locations to match v10 panel
    - Generated gerbers
2023-05-11 Moves production files to the production folder, zips them together
2023-05-11 Removes erroneous file depth
2023-05-11 Removes the panelizer instructions from the zip file

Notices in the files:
parts and their libraries:
SparkFun-Aesthetics: Licensing: Creative Commons ShareAlike 4.0 International - https://creativecommons.org/licenses/by-sa/4.0
SparkFun-Aesthetics: Released under the Creative Commons Attribution Share-Alike 4.0 License
SparkFun-Aesthetics: https://creativecommons.org/licenses/by-sa/4.0
